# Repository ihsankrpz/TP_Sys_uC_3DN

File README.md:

# TP_Sys_uC_3DN

This project is an learning project of using STM32L021K4T6 with KiCAD.
There is three part : 
	- Datasheets : All datashetts needed for the project
	- Firmware : STM32 firmware using STM32CubeIDE
	- Hardware : Conception with KiCAD.

# Hardware

#STM32L021K4T6
PB9 pin is connected to reset. L1,C4 and C5 is used to filter power supply.

#POWER SUPPLY
For the power supply, the datasheet indicated that all C's need to be more than 0.47uF.

#DAC
For DAC, in page 25, datasheet of MCP4801 indicates that C9 has to be 100n and C10 10u. 
not(CS) is the Chip Select input pin, which requires an active low to enable serial clock and data functions. 
not(LDAC) (latch DAC synchronization input) pin is used to transfer the input latch register to the DAC register (output latches, VOUT). 
When this pin is low, VOUT is updated with input register content. 
This pin can be tied to low (VSS) if the VOUT update is desired at the rising edge of the CS pin. 
This pin can be driven by an external control device such as an MCU I/O pin. 
MISO pin of SDI not used because STM32 is used Transmit only.

# Firmware

#LL drivers
Using LL drivers instead of using HAL drivers allows to use low-level registers to have beter optimisation.
LL drivers are specific to uC and HAL drivers are more portable.

#__STATIC_INLINE
__STATIC_INLINE is used to declare a function statically and the compiler will generate function only where necessary.

#Led_Timer
We have 32Mhz clock and we need to scale the timer at 1kHz clock. We choose PSC + ARR  = 32000.

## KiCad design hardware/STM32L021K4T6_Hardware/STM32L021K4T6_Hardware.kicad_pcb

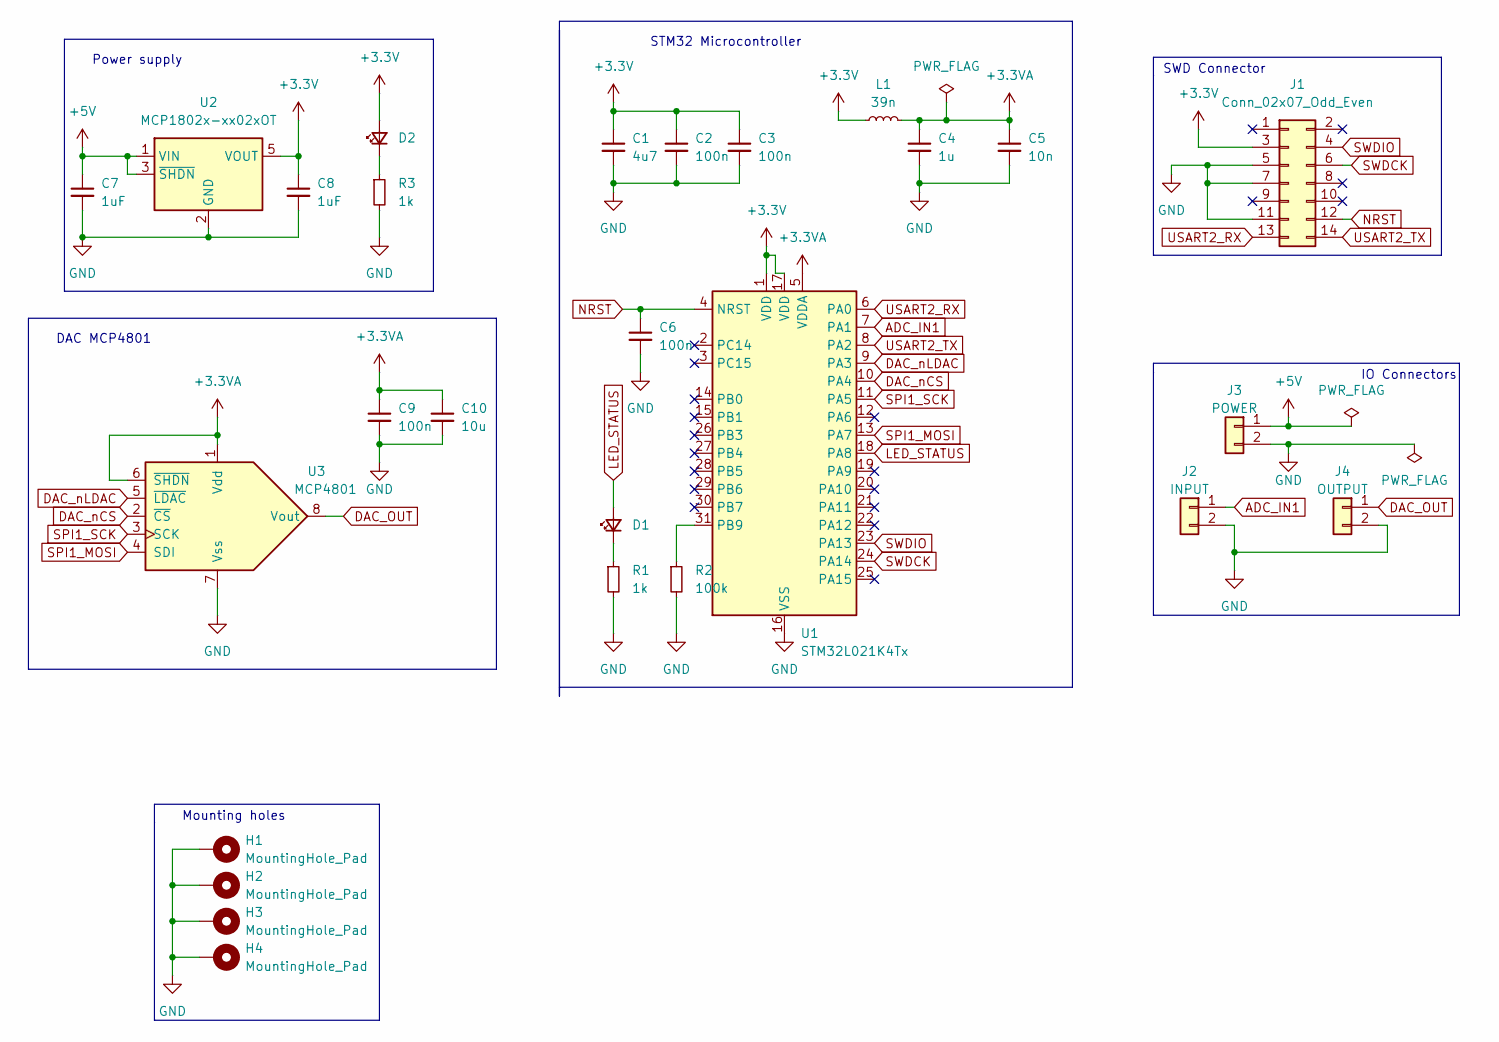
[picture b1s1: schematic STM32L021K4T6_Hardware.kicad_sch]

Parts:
C1: 4u7; C_0805_2012Metric_Pad1.18x1.45mm_HandSolder
C2, C3, C6, C9: 100n; C_0805_2012Metric_Pad1.18x1.45mm_HandSolder
C4: 1u; C_0805_2012Metric_Pad1.18x1.45mm_HandSolder
C5: 10n; C_0805_2012Metric_Pad1.18x1.45mm_HandSolder
C7, C8: 1uF; C_0805_2012Metric
C10: 10u; C_0805_2012Metric
D1, D2: LED_0603_1608Metric_Pad1.05x0.95mm_HandSolder
H1, H2, H3, H4: MountingHole_Pad; MountingHole_3.2mm_M3_Pad
J1: Conn_02x07_Odd_Even; PinHeader_2x07_P1.27mm_Vertical_SMD
J2: INPUT; JST_XH_B2B-XH-A_1x02_P2.50mm_Vertical
J3: POWER; JST_XH_B2B-XH-A_1x02_P2.50mm_Vertical
J4: OUTPUT; JST_XH_B2B-XH-A_1x02_P2.50mm_Vertical
L1: 39n; L_0805_2012Metric_Pad1.05x1.20mm_HandSolder
R1, R3: 1k; R_0805_2012Metric_Pad1.20x1.40mm_HandSolder
R2: 100k; R_0805_2012Metric_Pad1.20x1.40mm_HandSolder
U1: STM32L021K4Tx; LQFP-32_7x7mm_P0.8mm
U2: MCP1802x-xx02xOT; SOT-23-5
U3: MCP4801; SOIC-8_3.9x4.9mm_P1.27mm

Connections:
+3.3V: C1.1, C2.1, C3.1, C8.1, D2.2 (A), J1.3, L1.1, U1.1 (VDD), U1.17 (VDD), U2.5 (VOUT)
+3.3VA: C4.1, C5.1, C9.1, C10.1, L1.2, U1.5 (VDDA), U3.1 (Vdd), U3.6 (~SHDN)
+5V: C7.1, J3.1, U2.1 (VIN), U2.3 (~SHDN)
ADC_IN1: J2.1, U1.7 (PA1)
DAC_OUT: J4.1, U3.8 (Vout)
DAC_nCS: U1.10 (PA4), U3.2 (~CS)
DAC_nLDAC: U1.9 (PA3), U3.5 (~LDAC)
GND: C1.2, C2.2, C3.2, C4.2, C5.2, C6.2, C7.2, C8.2, C9.2, C10.2, H1.1, H2.1, H3.1, H4.1, J1.5, J1.7, J1.11, J2.2, J3.2, J4.2, R1.2, R2.2, R3.2, U1.16 (VSS), U1.32 (VSS), U2.2 (GND), U3.7 (Vss)
LED_STATUS: D1.2 (A), U1.18 (PA8)
NRST: C6.1, J1.12, U1.4 (NRST)
unnamed: D1.1 (K), R1.1
unnamed: D2.1 (K), R3.1
unnamed: R2.1, U1.31 (PB9)
SPI1_MOSI: U1.13 (PA7), U3.4 (SDI)
SPI1_SCK: U1.11 (PA5), U3.3 (SCK)
SWDCK: J1.6, U1.24 (PA14)
SWDIO: J1.4, U1.23 (PA13)
USART2_RX: J1.13, U1.6 (PA0)
USART2_TX: J1.14, U1.8 (PA2)

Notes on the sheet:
STM32 Microcontroller
IO Connectors
SWD Connector
Power supply
DAC MCP4801
Mounting holes

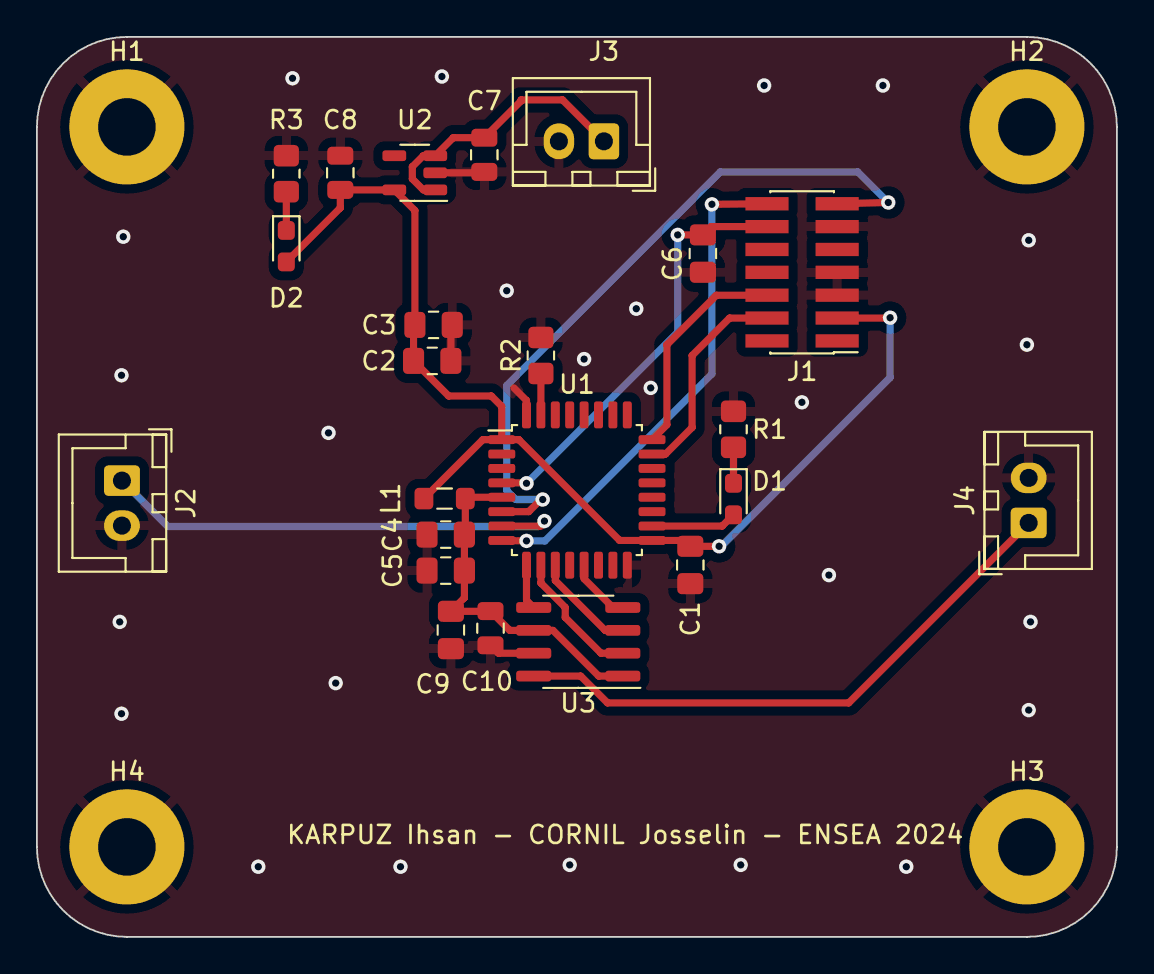
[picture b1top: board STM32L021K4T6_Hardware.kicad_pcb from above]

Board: 2 copper layers, 60.0 x 50.0 mm, 27 parts (0 on the bottom side), 19 nets.

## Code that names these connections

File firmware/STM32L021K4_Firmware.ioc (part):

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Mcu.Name=STM32L021K4Tx
Mcu.Package=LQFP32
Mcu.UserName=STM32L021K4Tx
PA0-CK_IN.Mode=Asynchronous
PA0-CK_IN.Signal=USART2_RX
PA1.Mode=IN1
PA1.Signal=ADC_IN1
PA13.Mode=Serial_Wire
PA13.Signal=SYS_SWDIO
PA14.Mode=Serial_Wire
PA14.Signal=SYS_SWCLK
PA2.Mode=Asynchronous
PA2.Signal=USART2_TX
PA3.GPIOParameters=GPIO_Label
PA3.GPIO_Label=DAC_nLDAC
PA3.Signal=GPIO_Output
PA4.GPIOParameters=GPIO_Label
PA4.GPIO_Label=DAC_nCS
PA4.Signal=GPIO_Output
PA5.Mode=TX_Only_Simplex_Unidirect_Master
PA5.Signal=SPI1_SCK
PA7.Mode=TX_Only_Simplex_Unidirect_Master
PA7.Signal=SPI1_MOSI
PA8.Signal=S_TIM2_CH1
RCC.HSE_VALUE=8000000
RCC.SYSCLKFreq_VALUE=32000000
RCC.SYSCLKSource=RCC_SYSCLKSOURCE_PLLCLK
board=custom

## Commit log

2024-02-09 commit datasheets and first firmware
2024-02-09 pinout stm32
2024-02-09 schematic and footprints
2024-02-09 add mounting holes
2024-02-09 sav_09_02_2024_12_04
2024-02-09 routage-ratnest
2024-02-09 sav_09_02_2024_22_45_drc_check
2024-02-10 drc_check_ok
2024-02-29 drc check bis
2024-02-29 drc check ok bis bis
2024-02-29 J3 reversed
2024-03-14 led test
2024-03-14 update led test with interrupt
2024-03-14 add usart2
2024-03-14 sav_14_03_2024 sav:AnalogInput not fonctional
